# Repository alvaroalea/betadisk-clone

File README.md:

# The Beta 128K Interface Disk for ZX Spectrum
the schematic and PCB for this interfaz, make in KICAD
Including gerber files to direct order, the PCB is just 15x10cm.

# THIS IS WORK IN PROGRESS.ACTUALY THIS INTERFACE DO NOT WORK!!!!! BE AWARE
## NOT FOR USE, THIS IS ONLY A MOCKUP, WORK IN PROGRESS

(C) 2018 Alvaro Alea Fernandez.

This work is licensed under a Creative Commons Attribution-NonCommercial-ShareAlike 4.0 International License.

http://creativecommons.org/licenses/by-nc-sa/4.0/

BOM is probably not acurrate, gerbers have names wrong.

GAL code is not checked

Even this interface provide a back conector for other interfaces, it do not provide a good IORQ signals, so can be incompatible with other interfaces that original interface is working good.

This board hide the serial port on +2.

The Advantege of this interfaz over the original are:

- 4 Banks of ROM, so you can swap between diferent versiones of TR-Dos. selectable by dip-switches
  (TR-DOS 5.03 and 5.04T with fixed, TR-DOS 6.04 & velesoft 5.03 with monitor.

- Posibility of use crossed and plain floppy cable, and invert Drive 1 and Drive 2, very usefull if you have a Gotek and a real floppy.

- Jumper for swap D0 & D7 (because some roms are distributed with this bits swapeed)

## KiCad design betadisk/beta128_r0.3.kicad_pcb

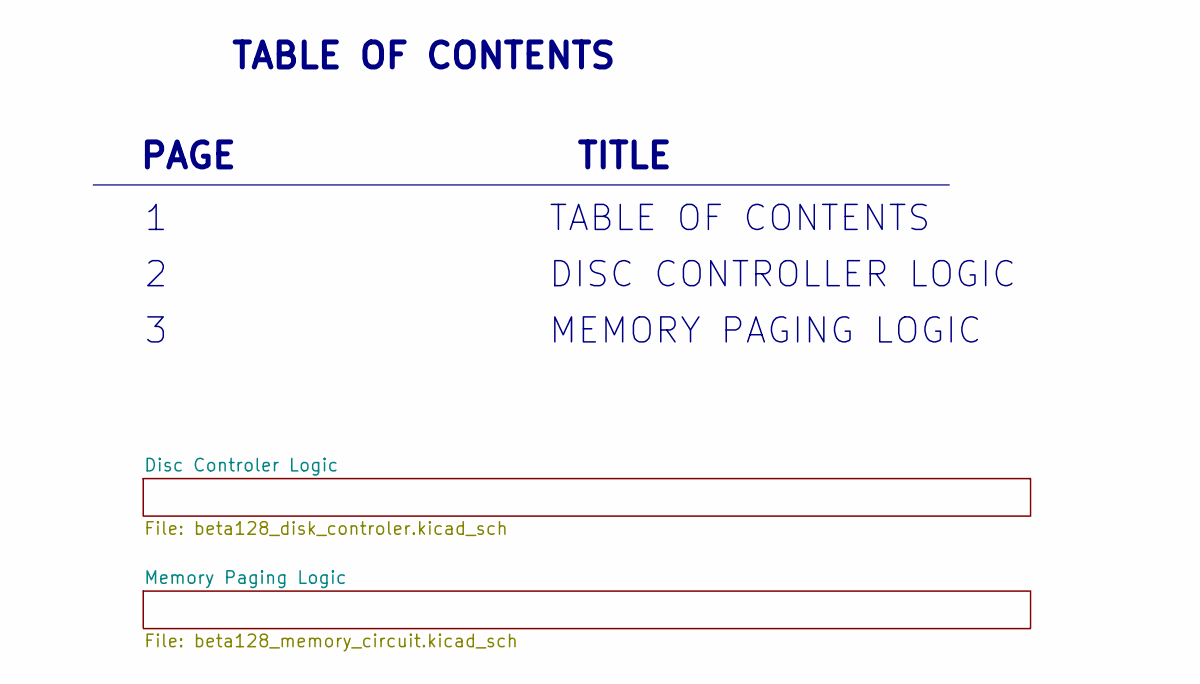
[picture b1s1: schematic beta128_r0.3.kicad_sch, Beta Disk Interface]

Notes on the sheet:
1 TABLE OF CONTENTS
2 DISC CONTROLLER LOGIC
3 MEMORY PAGING LOGIC
TABLE OF CONTENTS
PAGE TITLE

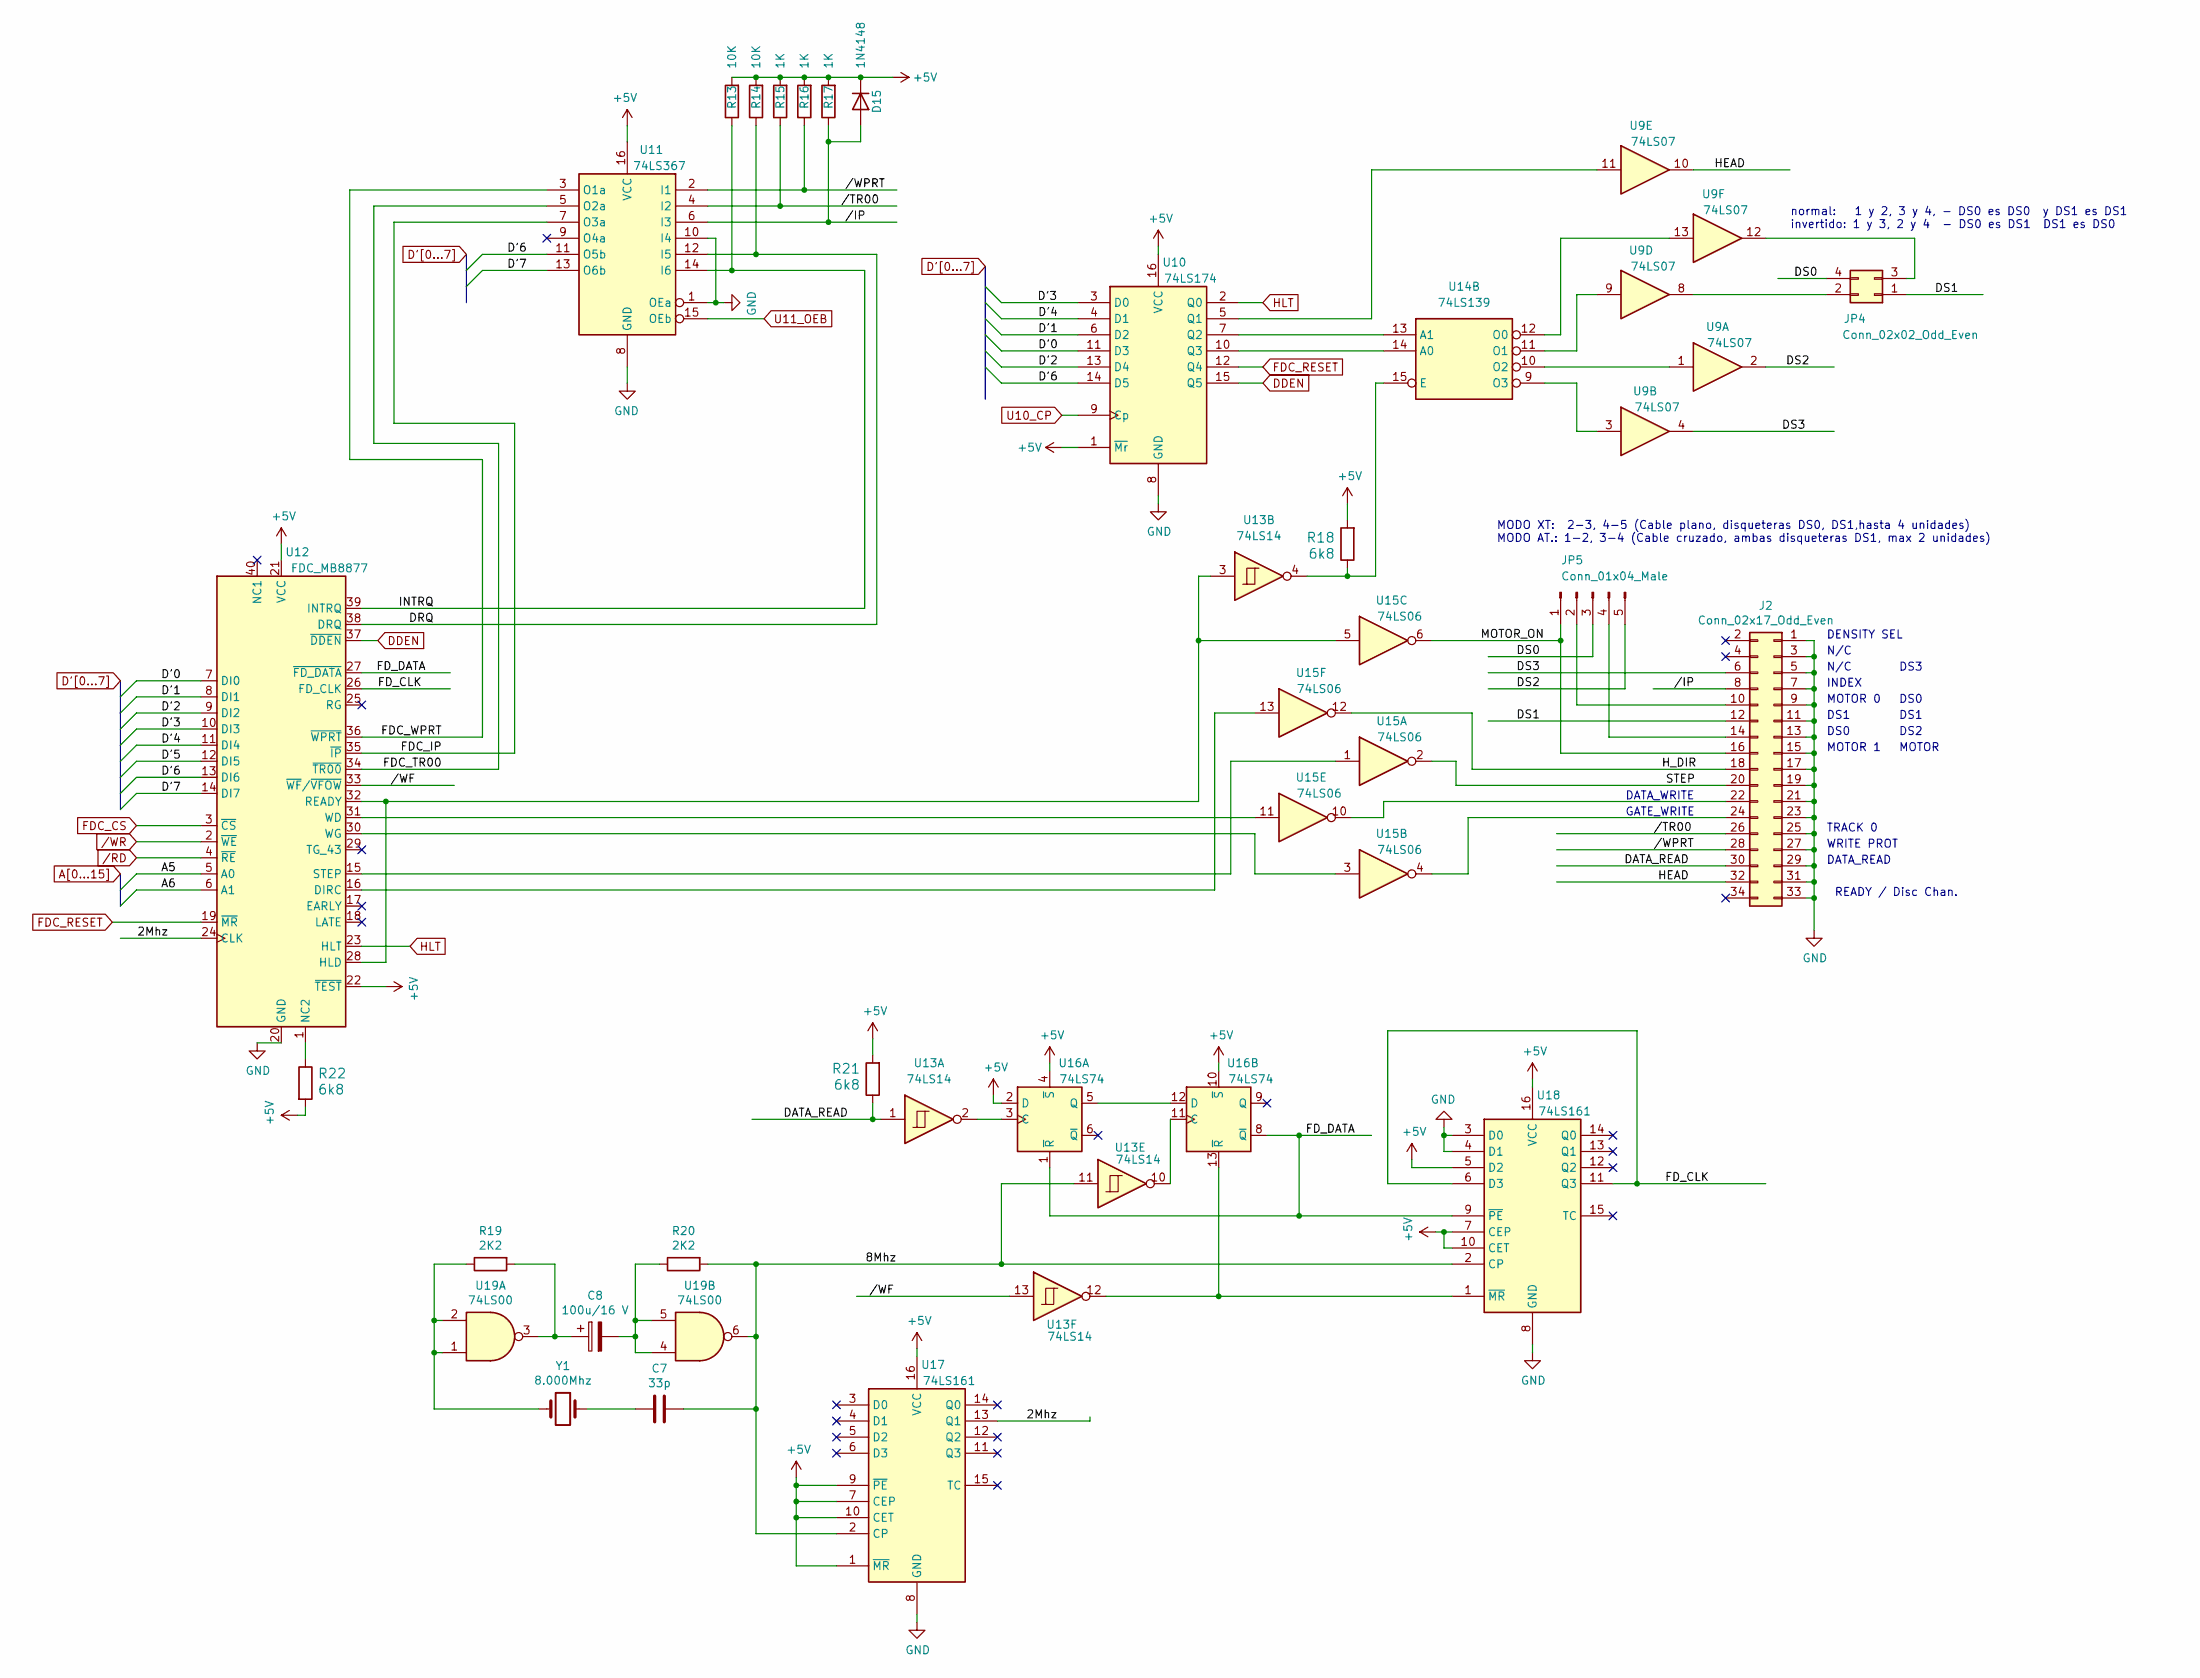
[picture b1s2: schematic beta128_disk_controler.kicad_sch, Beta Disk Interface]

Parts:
C7: 33p; C_Disc_D5.0mm_W2.5mm_P5.00mm
C8: 100u/16 V; CP_Radial_D7.5mm_P2.50mm
D15: 1N4148; D_DO-35_SOD27_P7.62mm_Horizontal
J2: Conn_02x17_Odd_Even; PinHeader_2x17_P2.54mm_Vertical
JP4: Conn_02x02_Odd_Even; PinHeader_2x02_P2.54mm_Vertical
JP5: Conn_01x04_Male; PinHeader_1x05_P2.54mm_Vertical
R13, R14: 10K; R_Axial_DIN0207_L6.3mm_D2.5mm_P7.62mm_Horizontal
R15, R16, R17: 1K; R_Axial_DIN0207_L6.3mm_D2.5mm_P7.62mm_Horizontal
R18, R21, R22: 6k8; R_Axial_DIN0207_L6.3mm_D2.5mm_P7.62mm_Horizontal
R19, R20: 2K2; R_Axial_DIN0207_L6.3mm_D2.5mm_P7.62mm_Horizontal
U9: 74LS07; DIP-14_W7.62mm_LongPads
U10: 74LS174; DIP-16_W7.62mm_LongPads
U11: 74LS367; DIP-16_W7.62mm_LongPads
U12: FDC_MB8877; DIP-40_W15.24mm_LongPads
U13: 74LS14; DIP-14_W7.62mm_LongPads
U14: 74LS139; DIP-16_W7.62mm_LongPads
U15: 74LS06; DIP-14_W7.62mm_LongPads
U16: 74LS74; DIP-14_W7.62mm_LongPads
U17, U18: 74LS161; DIP-16_W7.62mm_LongPads
U19: 74LS00; DIP-14_W7.62mm_LongPads
Y1: 8.000Mhz; Crystal_HC18-U_Vertical

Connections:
+5V: D15.1 (K), R13.2, R14.2, R15.2, R16.2, R17.2, R18.2, R21.2, R22.2, U10.1 (~Mr), U10.16 (VCC), U11.16 (VCC), U12.21 (VCC), U12.22 (~TEST), U16.2 (D), U16.4 (~S), U16.10 (~S), U17.1 (~MR), U17.7 (CEP), U17.9 (~PE), U17.10 (CET), U17.16 (VCC), U18.5 (D2), U18.7 (CEP), U18.10 (CET), U18.16 (VCC); also elsewhere on the board
/Disc Controler Logic/2Mhz: U12.24 (CLK), U17.13 (Q1)
/Disc Controler Logic/8Mhz: C7.2, R20.2, U13.11, U17.2 (CP), U18.2 (CP), U19.6
/Disc Controler Logic//IP: D15.2 (A), J2.8, R17.1, U11.6 (I3)
/Disc Controler Logic//TR00: J2.26, R15.1, U11.4 (I2)
/Disc Controler Logic//WF: U12.33 (~WF~/~VFOW), U13.13
/Disc Controler Logic//WPRT: J2.28, R16.1, U11.2 (I1)
/Disc Controler Logic/DATA_READ: J2.30, R21.1, U13.1
/Disc Controler Logic/DRQ: R14.1, U11.12 (I5), U12.38 (DRQ)
/Disc Controler Logic/DS0: JP4.4, JP5.3
/Disc Controler Logic/DS1: J2.12, JP4.1
/Disc Controler Logic/DS2: JP5.5, U9.2
/Disc Controler Logic/DS3: J2.6, U9.4
/Disc Controler Logic/FDC_IP: U11.7 (O3a), U12.35 (~IP)
/Disc Controler Logic/FDC_TR00: U11.5 (O2a), U12.34 (~TR00)
/Disc Controler Logic/FDC_WPRT: U11.3 (O1a), U12.36 (~WPRT)
/Disc Controler Logic/FD_CLK: U12.26 (FD_CLK), U18.6 (D3), U18.11 (Q3)
/Disc Controler Logic/FD_DATA: U12.27 (~FD_DATA), U16.1 (~R), U16.8 (~Q), U18.9 (~PE)
/Disc Controler Logic/HEAD: J2.32, U9.10
/Disc Controler Logic/H_DIR: J2.18, U15.12
/Disc Controler Logic/INTRQ: R13.1, U11.14 (I6), U12.39 (INTRQ)
/Disc Controler Logic/MOTOR_ON: J2.16, JP5.1, U15.6
/Disc Controler Logic/STEP: J2.20, U15.2
/RD: U12.4 (~RE); also elsewhere on the board
/WR: U12.2 (~WE); also elsewhere on the board
A5: U12.5 (A0); also elsewhere on the board
A6: U12.6 (A1); also elsewhere on the board
D'0: U10.11 (D3), U12.7 (DI0); also elsewhere on the board
D'1: U10.6 (D2), U12.8 (DI1); also elsewhere on the board
D'2: U10.13 (D4), U12.9 (DI2); also elsewhere on the board
D'3: U10.3 (D0), U12.10 (DI3); also elsewhere on the board
D'4: U10.4 (D1), U12.11 (DI4); also elsewhere on the board
D'5: U12.12 (DI5); also elsewhere on the board
D'6: U10.14 (D5), U11.11 (O5b), U12.13 (DI6); also elsewhere on the board
D'7: U11.13 (O6b), U12.14 (DI7); also elsewhere on the board
DDEN: U10.15 (Q5), U12.37 (~DDEN)
FDC_CS: U12.3 (~CS); also elsewhere on the board
FDC_RESET: U10.12 (Q4), U12.19 (~MR)
GND: J2.1, J2.3, J2.5, J2.7, J2.9, J2.11, J2.13, J2.15, J2.17, J2.19, J2.21, J2.23, J2.25, J2.27, J2.29, J2.31, J2.33, U10.8 (GND), U11.1 (OEa), U11.8 (GND), U11.10 (I4), U12.20 (GND), U17.8 (GND), U18.3 (D0), U18.4 (D1), U18.8 (GND); also elsewhere on the board
HLT: U10.2 (Q0), U12.23 (HLT)
unnamed: C7.1, Y1.1
unnamed: C8.1, R19.2, U19.3
unnamed: C8.2, R20.1, U19.4, U19.5
unnamed: J2.10, JP5.2
unnamed: J2.14, JP5.4
unnamed: J2.22, U15.10
unnamed: J2.24, U15.4
unnamed: JP4.2, U9.8
unnamed: JP4.3, U9.12
unnamed: R18.1, U13.4, U14.15 (E)
unnamed: R19.1, U19.1, U19.2, Y1.2
unnamed: R22.1, U12.1 (NC2)
unnamed: U9.11, U10.5 (Q1)
unnamed: U10.7 (Q2), U14.13 (A1)
unnamed: U10.10 (Q3), U14.14 (A0)
unnamed: U12.15 (STEP), U15.1
unnamed: U12.16 (DIRC), U15.13
unnamed: U12.28 (HLD), U12.32 (READY), U13.3, U15.5
unnamed: U12.30 (WG), U15.3
unnamed: U12.31 (WD), U15.11
unnamed: U13.2, U16.3 (C)
unnamed: U13.10, U16.11 (C)
unnamed: U13.12, U16.13 (~R), U18.1 (~MR)
unnamed: U9.3, U14.9 (O3)
unnamed: U9.1, U14.10 (O2)
unnamed: U9.9, U14.11 (O1)
unnamed: U9.13, U14.12 (O0)
unnamed: U16.5 (Q), U16.12 (D)
U10_CP: U10.9 (Cp); also elsewhere on the board
U11_OEB: U11.15 (OEb); also elsewhere on the board

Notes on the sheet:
MODO XT: 2-3, 4-5 (Cable plano, disqueteras DS0, DS1,hasta 4 unidades) MODO AT.: 1-2, 3-4 (Cable cruzado, ambas disqueteras DS1, max 2 unidades)
DATA_WRITE
GATE_WRITE
normal: 1 y 2, 3 y 4, - DS0 es DS0 y DS1 es DS1 invertido: 1 y 3, 2 y 4 - DS0 es DS1 DS1 es DS0
DENSITY SEL
N/C
INDEX
MOTOR 0
DS1
DS0
MOTOR 1
TRACK 0
WRITE PROT
DATA_READ
READY / Disc Chan.
DS3
DS0
DS2
MOTOR

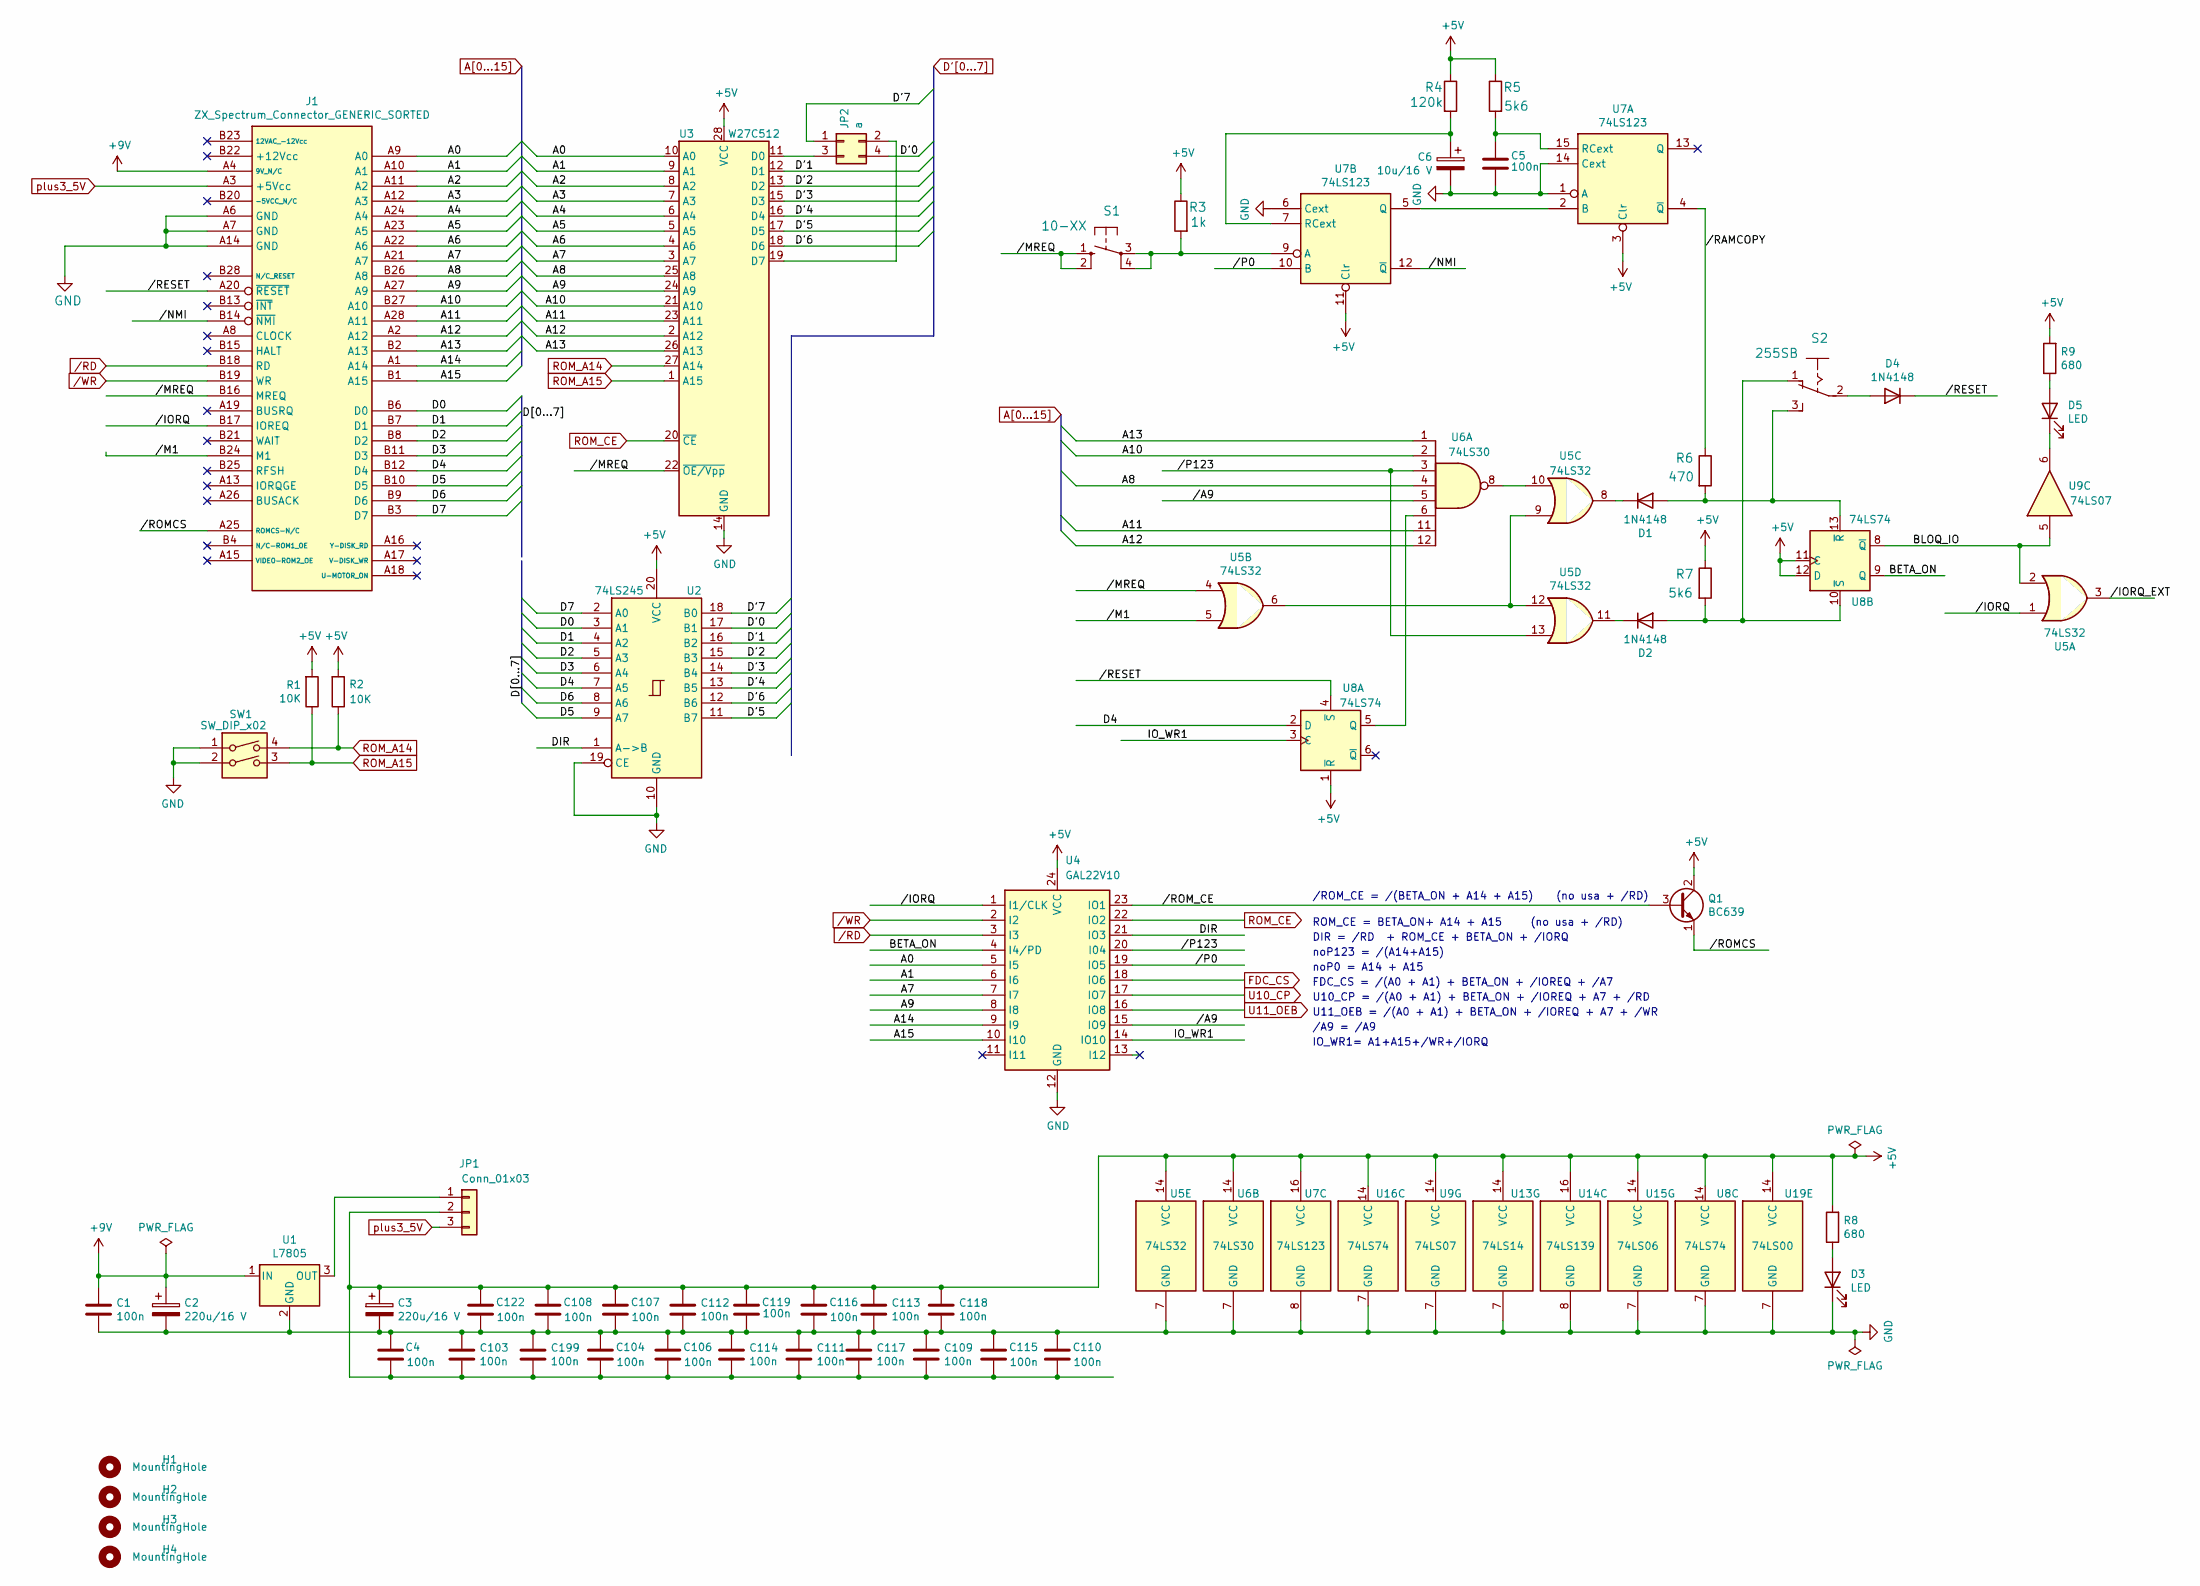
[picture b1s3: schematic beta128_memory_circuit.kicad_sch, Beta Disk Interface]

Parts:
C1, C4, C5, C103, C104, C106, C107, C108, C109, C110, C111, C112, C113, C114, C115, C116, C117, C118, C119, C122, C199: 100n; C_Disc_D5.0mm_W2.5mm_P5.00mm
C2, C3: 220u/16 V; CP_Radial_D7.5mm_P2.50mm
C6: 10u/16 V; CP_Radial_D7.5mm_P2.50mm
D1, D2, D4: 1N4148; D_DO-35_SOD27_P7.62mm_Horizontal
D3, D5: LED; LED_D5.0mm
H1, H2, H3, H4: MountingHole; MountingHole_3mm
J1: ZX_Spectrum_Connector_GENERIC_SORTED; ZX_EDGE_90extend
JP1: Conn_01x03; PinHeader_1x03_P2.54mm_Vertical
JP2: a; PinHeader_2x02_P2.54mm_Vertical
Q1: BC639; TO-92_Inline
R1, R2: 10K; R_Axial_DIN0207_L6.3mm_D2.5mm_P7.62mm_Horizontal
R3: 1k; R_Axial_DIN0207_L6.3mm_D2.5mm_P7.62mm_Horizontal
R4: 120k; R_Axial_DIN0207_L6.3mm_D2.5mm_P7.62mm_Horizontal
R5, R7: 5k6; R_Axial_DIN0207_L6.3mm_D2.5mm_P7.62mm_Horizontal
R6: 470; R_Axial_DIN0207_L6.3mm_D2.5mm_P7.62mm_Horizontal
R8, R9: 680; R_Axial_DIN0207_L6.3mm_D2.5mm_P7.62mm_Horizontal
S1: 10-XX; SW_TH_Tactile_Omron_B3F-10xx
S2: 255SB; SW_C&K_710x-xx-xx-Z-_SPDT
SW1: SW_DIP_x02; SW_DIP_SPSTx02_Slide_9.78x7.26mm_W7.62mm_P2.54mm
U1: L7805; TO-220-3_Vertical
U2: 74LS245; DIP-20_W7.62mm_LongPads
U3: W27C512; DIP-28_W15.24mm_LongPads
U4: GAL22V10; DIP-24_W7.62mm_LongPads
U5: 74LS32; DIP-14_W7.62mm_LongPads
U6: 74LS30; DIP-14_W7.62mm_LongPads
U7: 74LS123; DIP-16_W7.62mm_LongPads
U8, U16: 74LS74; DIP-14_W7.62mm_LongPads
U9: 74LS07; DIP-14_W7.62mm_LongPads
U13: 74LS14; DIP-14_W7.62mm_LongPads
U14: 74LS139; DIP-16_W7.62mm_LongPads
U15: 74LS06; DIP-14_W7.62mm_LongPads
U19: 74LS00; DIP-14_W7.62mm_LongPads

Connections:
+5V: C3.1, C4.2, C103.1, C104.2, C106.2, C107.1, C108.1, C109.1, C110.2, C111.1, C112.2, C113.2, C114.1, C115.2, C116.1, C117.1, C118.2, C119.1, C122.1, C199.1, JP1.2, Q1.2 (C), R1.2, R2.2, R3.1, R4.1, R5.1, R7.1, R8.2, R9.2, U2.20 (VCC), U3.28 (VCC), U4.24 (VCC), U5.14 (VCC), U6.14 (VCC), U7.3 (Clr), U7.11 (Clr), U7.16 (VCC), U8.1 (~R), U8.11 (C), U8.12 (D), U8.14 (VCC), U9.14 (VCC), U13.14 (VCC), U14.16 (VCC), U15.14 (VCC), U16.14 (VCC), U19.14 (VCC); also elsewhere on the board
+9V: C1.2, C2.1, J1.A4 (9V_N/C), U1.1 (IN)
/Memory Paging Logic//A9: U4.15 (IO9), U6.5
/Memory Paging Logic//IORQ: J1.B17 (IOREQ), U4.1 (I1/CLK), U5.1
/Memory Paging Logic//M1: J1.B24 (M1), U5.5
/Memory Paging Logic//MREQ: J1.B16 (MREQ), S1.1 (S), S1.2 (S1), U3.22 (~OE/Vpp), U5.4
/Memory Paging Logic//NMI: J1.B14 (~NMI), U7.12 (~Q)
/Memory Paging Logic//P0: U4.19 (IO5), U7.10 (B)
/Memory Paging Logic//P123: U4.20 (I04), U5.13, U6.3
/Memory Paging Logic//RAMCOPY: R6.1, U7.4 (~Q)
/Memory Paging Logic//RESET: D4.1 (K), J1.A20 (~RESET), U8.4 (~S)
/Memory Paging Logic//ROMCS: J1.A25 (ROMCS-N/C), Q1.1 (E)
/Memory Paging Logic//ROM_CE: Q1.3 (B), U4.23 (IO1)
/Memory Paging Logic/BETA_ON: U4.4 (I4/PD), U8.9 (Q)
/Memory Paging Logic/BLOQ_IO: U5.2, U8.8 (~Q), U9.5
/Memory Paging Logic/D0: J1.B6 (D0), U2.3 (A1)
/Memory Paging Logic/D1: J1.B7 (D1), U2.4 (A2)
/Memory Paging Logic/D2: J1.B8 (D2), U2.5 (A3)
/Memory Paging Logic/D3: J1.B11 (D3), U2.6 (A4)
/Memory Paging Logic/D4: J1.B12 (D4), U2.7 (A5), U8.2 (D)
/Memory Paging Logic/D5: J1.B10 (D5), U2.9 (A7)
/Memory Paging Logic/D6: J1.B9 (D6), U2.8 (A6)
/Memory Paging Logic/D7: J1.B3 (D7), U2.2 (A0)
/Memory Paging Logic/DIR: U2.1 (A->B), U4.21 (IO3)
/Memory Paging Logic/IO_WR1: U4.14 (IO10), U8.3 (C)
/RD: J1.B18 (RD), U4.3 (I3); also elsewhere on the board
/WR: J1.B19 (WR), U4.2 (I2); also elsewhere on the board
A0: J1.A9 (A0), U3.10 (A0), U4.5 (I5)
A1: J1.A10 (A1), U3.9 (A1), U4.6 (I6)
A2: J1.A11 (A2), U3.8 (A2)
A3: J1.A12 (A3), U3.7 (A3)
A4: J1.A24 (A4), U3.6 (A4)
A5: J1.A23 (A5), U3.5 (A5); also elsewhere on the board
A6: J1.A22 (A6), U3.4 (A6); also elsewhere on the board
A7: J1.A21 (A7), U3.3 (A7), U4.7 (I7)
A8: J1.B26 (A8), U3.25 (A8), U6.4
A9: J1.A27 (A9), U3.24 (A9), U4.8 (I8)
A10: J1.B27 (A10), U3.21 (A10), U6.2
A11: J1.A28 (A11), U3.23 (A11), U6.11
A12: J1.A2 (A12), U3.2 (A12), U6.12
A13: J1.B2 (A13), U3.26 (A13), U6.1
A14: J1.A1 (A14), U4.9 (I9)
A15: J1.B1 (A15), U4.10 (I10)
D'0: JP2.4, U2.17 (B1); also elsewhere on the board
D'1: U2.16 (B2), U3.12 (D1); also elsewhere on the board
D'2: U2.15 (B3), U3.13 (D2); also elsewhere on the board
D'3: U2.14 (B4), U3.15 (D3); also elsewhere on the board
D'4: U2.13 (B5), U3.16 (D4); also elsewhere on the board
D'5: U2.11 (B7), U3.17 (D5); also elsewhere on the board
D'6: U2.12 (B6), U3.18 (D6); also elsewhere on the board
D'7: JP2.1, U2.18 (B0); also elsewhere on the board
FDC_CS: U4.18 (IO6); also elsewhere on the board
GND: C1.1, C2.2, C3.2, C4.1, C5.2, C6.2, C103.2, C104.1, C106.1, C107.2, C108.2, C109.2, C110.1, C111.2, C112.1, C113.1, C114.2, C115.1, C116.2, C117.2, C118.1, C119.2, C122.2, C199.2, D3.1 (K), J1.A6 (GND), J1.A7 (GND), J1.A14 (GND), SW1.1, SW1.2, U1.2 (GND), U2.10 (GND), U2.19 (CE), U3.14 (GND), U4.12 (GND), U5.7 (GND), U6.7 (GND), U7.1 (A), U7.6 (Cext), U7.8 (GND), U7.14 (Cext), U8.7 (GND), U9.7 (GND), U13.7 (GND), U14.8 (GND), U15.7 (GND), U16.7 (GND), U19.7 (GND); also elsewhere on the board
unnamed: C5.1, R5.2, U7.15 (RCext)
unnamed: C6.1, R4.2, U7.7 (RCext)
unnamed: D1.1 (K), U5.8
unnamed: D1.2 (A), R6.2, S2.3 (S), U8.13 (~R)
unnamed: D2.1 (K), U5.11
unnamed: D2.2 (A), R7.2, S2.1 (O), U8.10 (~S)
unnamed: D3.2 (A), R8.1
unnamed: D4.2 (A), S2.2
unnamed: D5.1 (K), U9.6
unnamed: D5.2 (A), R9.1
unnamed: JP1.1, U1.3 (OUT)
unnamed: JP2.2, U3.19 (D7)
unnamed: JP2.3, U3.11 (D0)
unnamed: R3.2, S1.3, S1.4 (P1), U7.9 (A)
unnamed: U5.10, U6.8
unnamed: U5.6, U5.9, U5.12
unnamed: U6.6, U8.5 (Q)
unnamed: U7.2 (B), U7.5 (Q)
ROM_A14: R2.1, SW1.4, U3.27 (A14)
ROM_A15: R1.1, SW1.3, U3.1 (A15)
ROM_CE: U3.20 (~CE), U4.22 (IO2)
U10_CP: U4.17 (IO7); also elsewhere on the board
U11_OEB: U4.16 (IO8); also elsewhere on the board
plus3_5V: J1.A3 (+5Vcc), JP1.3

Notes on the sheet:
/ROM_CE = /(BETA_ON + A14 + A15) (no usa + /RD)
ROM_CE = BETA_ON+ A14 + A15 (no usa + /RD)
DIR = /RD + ROM_CE + BETA_ON + /IORQ
noP123 = /(A14+A15)
noP0 = A14 + A15
FDC_CS = /(A0 + A1) + BETA_ON + /IOREQ + /A7
U10_CP = /(A0 + A1) + BETA_ON + /IOREQ + A7 + /RD
U11_OEB = /(A0 + A1) + BETA_ON + /IOREQ + A7 + /WR
/A9 = /A9
IO_WR1= A1+A15+/WR+/IORQ

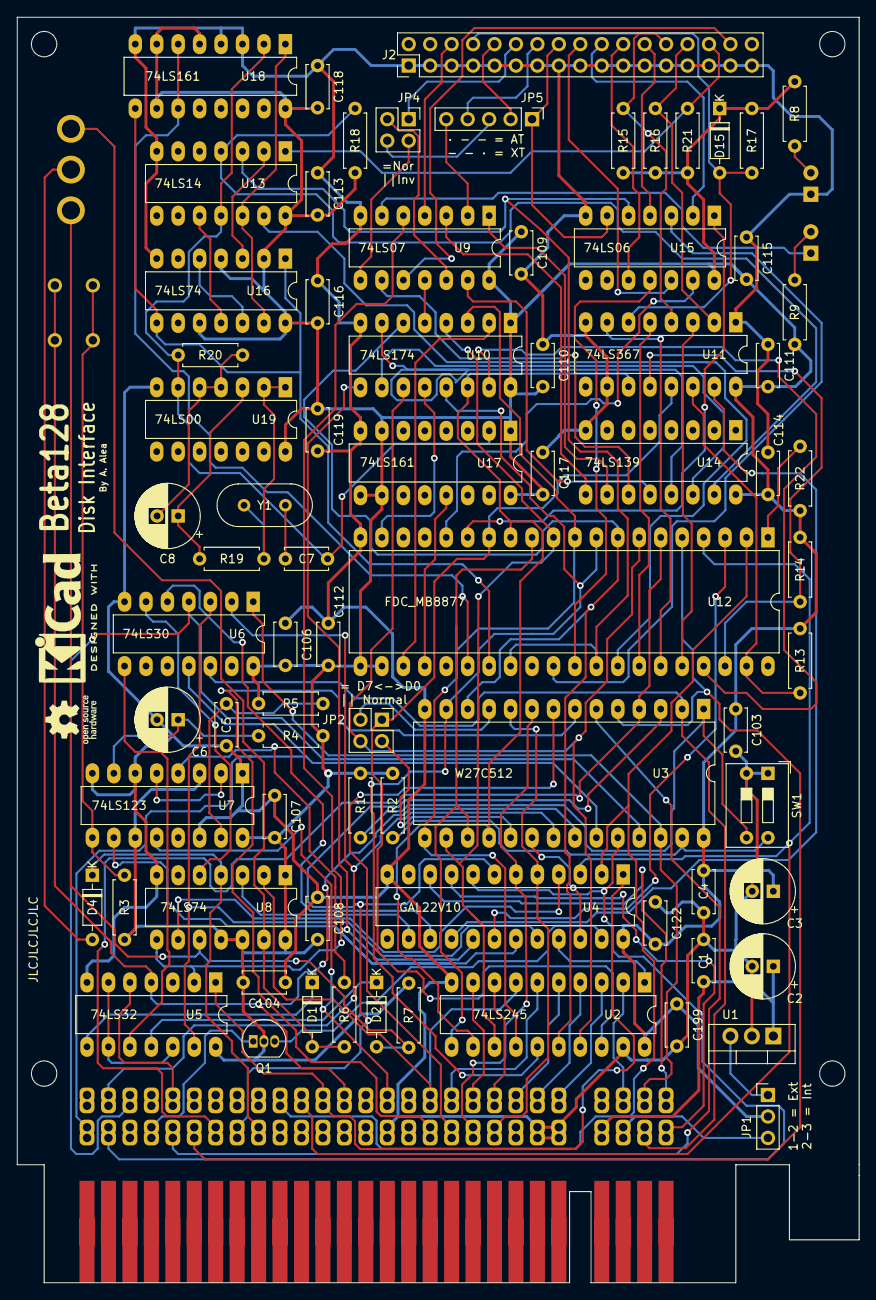
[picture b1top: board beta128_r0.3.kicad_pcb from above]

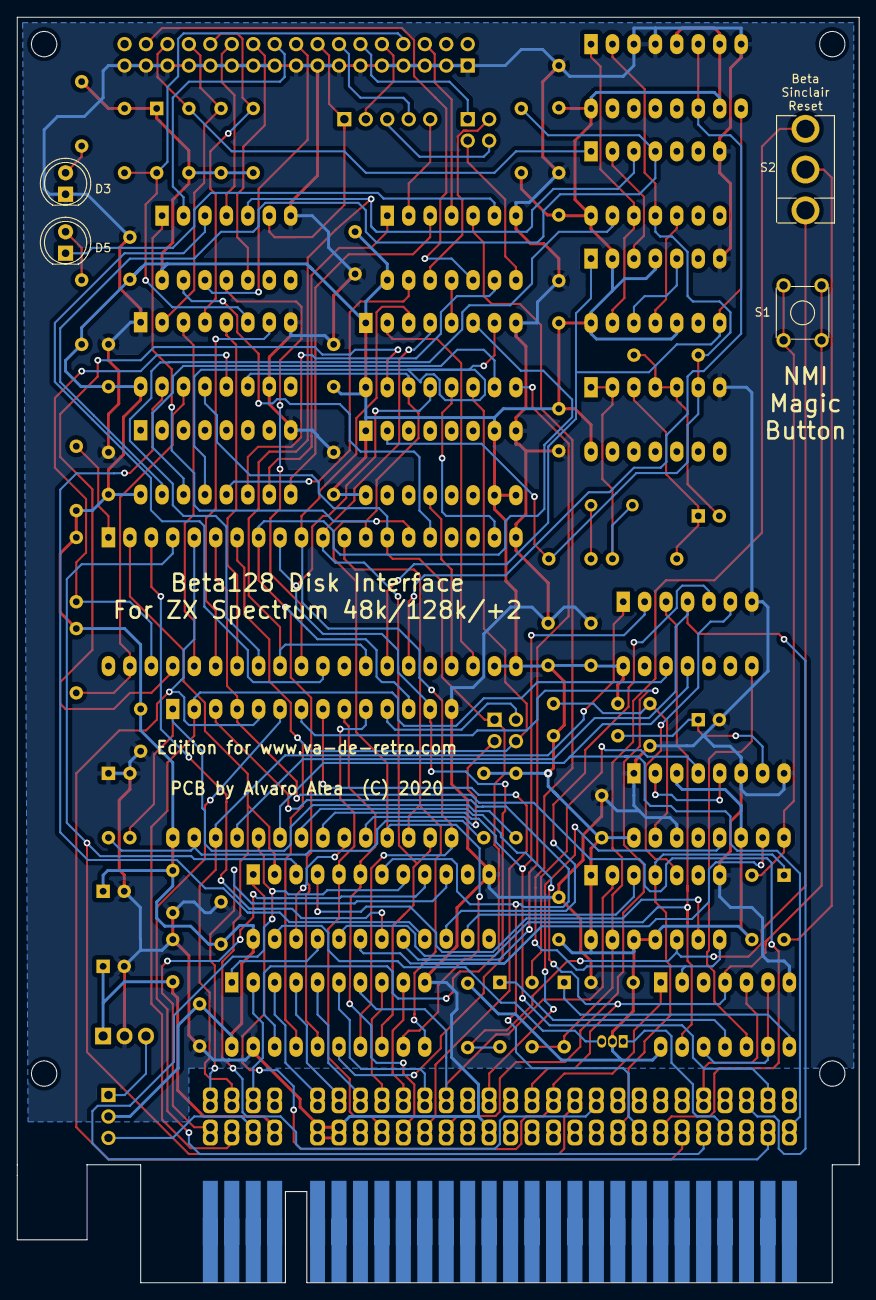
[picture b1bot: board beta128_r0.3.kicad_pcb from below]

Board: 2 copper layers, 99.7 x 149.9 mm, 89 parts (6 on the bottom side), 130 nets.

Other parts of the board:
REF1: KiCad-Logo2_6mm_SilkScreen
REF2: OSHW-Logo_5.7x6mm_SilkScreen
ZX-EDGE_2, ZX-EDGE_3: ZX_EDGE

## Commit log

2020-03-08 initial
2020-03-08 add schematic
2020-03-11 update on libs
2020-03-12 gal code
2020-03-12 schematic in pdf
2020-03-20 update gal code
2020-03-20 now gal compile
2020-04-08 add roms to burn
2020-04-08 fix duplicate_label
2020-05-08 fix 74ls00 power pins
2022-02-13 update (C)

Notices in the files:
README.md:
CC BY-NC-SA 4.0
betadisk/beta128_disk_controler.kicad_sch:
Under Licence GPL3
betadisk/beta128_r0.3.kicad_pcb:
PCB by Alvaro Alea  (C) 2020
